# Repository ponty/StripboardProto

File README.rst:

StripboardProto

Stripboard_ based modular hardware prototyping system.

Links:
 * home: https://github.com/ponty/StripboardProto
 * documentation: http://ponty.github.com/StripboardProto

Features:
 - designed for hobby projects
 - stripboard_ based
 - no drilling
 - no etching
 - modular 
 - the bus consists of 8 bit ports
 - passive backplane_ holds the modules
 - Design tool: `EAGLE Light Edition`_
 
Example::

    backplane 
    
    II
    II
    II=C=================      microcontroller module    
    II
    II
    II=C=================      sound module
    II
    II
    II=C=================      USB module
    II

Bus:: 

    -----------------------------------------------               -----------
    | Port 1                                      |               | Port 2 
    -------------------------------------------------------------------------
    | 0 | 1 | 2 | 3 | 4 | 5 | 6 | 7 | POWER | GND | EMPTY | EMPTY | 0 | 1 ... 
    -------------------------------------------------------------------------

other modular designs:
 - http://www.instructables.com/id/AVR-mini-board-with-additional-boards/
 - Arduino shield

.. _`EAGLE Light Edition`: http://www.cadsoftusa.com/freeware.htm
.. _`Backplane`: http://en.wikipedia.org/wiki/Backplane
.. _Stripboard: http://en.wikipedia.org/wiki/Stripboard

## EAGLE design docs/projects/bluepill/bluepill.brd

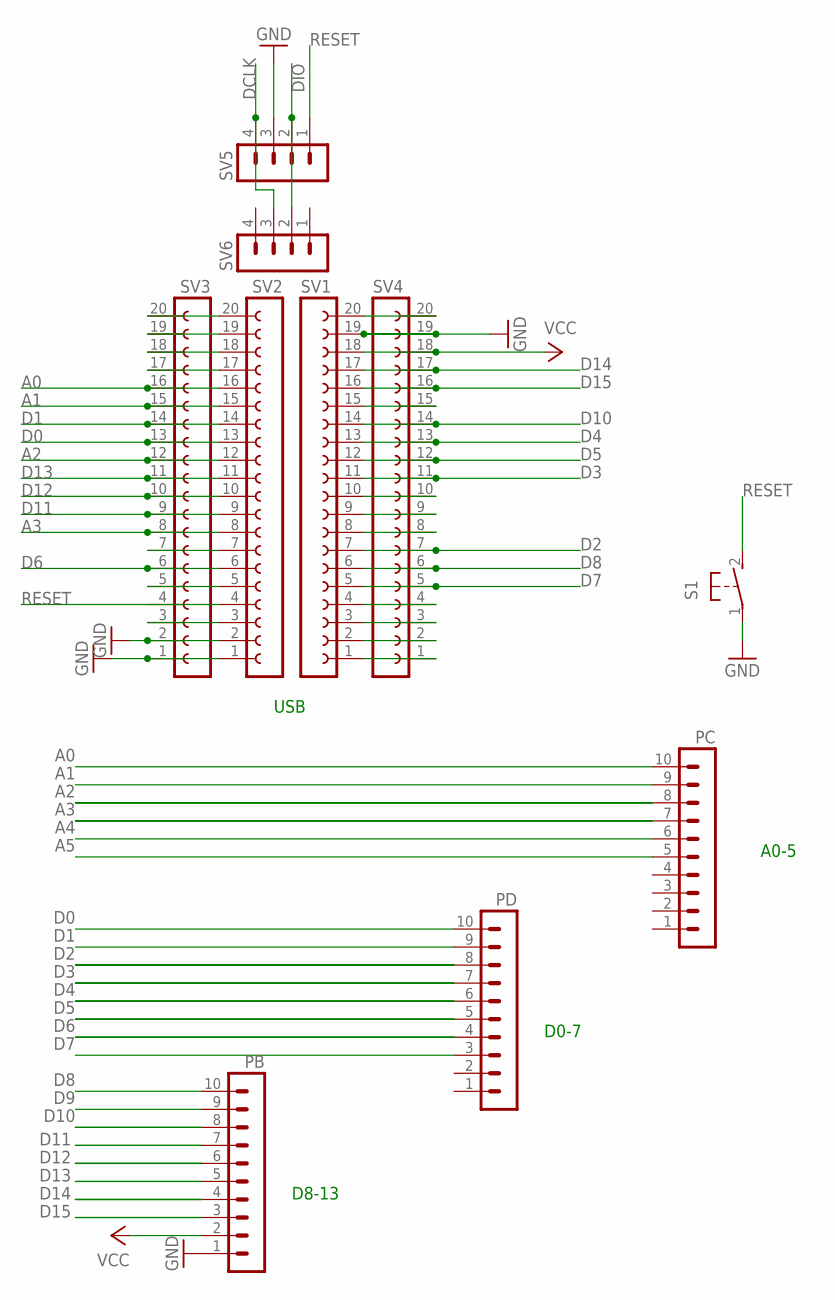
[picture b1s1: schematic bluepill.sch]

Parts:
PB: MA10-1W
PC: MA10-1W
PD: MA10-1W
S1: 31-XX; B3F-31XX
SV1, SV2, SV3, SV4: FE20-1; FE20
SV5, SV6: MA04-1

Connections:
A0: PC.10, SV2.16, SV3.16
A1: PC.9, SV2.15, SV3.15
A2: PC.8, SV2.12, SV3.12
A3: PC.7, SV2.8, SV3.8
A4: PC.6
A5: PC.5
D0: PD.10, SV2.13, SV3.13
D1: PD.9, SV2.14, SV3.14
D2: PD.8, SV1.7, SV4.7
D3: PD.7, SV1.11, SV4.11
D4: PD.6, SV1.13, SV4.13
D5: PD.5, SV1.12, SV4.12
D6: PD.4, SV2.6, SV3.6
D7: PD.3, SV1.5, SV4.5
D8: PB.10, SV1.6, SV4.6
D9: PB.9
D10: PB.8, SV1.14, SV4.14
D11: PB.7, SV2.9, SV3.9
D12: PB.6, SV2.10, SV3.10
D13: PB.5, SV2.11, SV3.11
D14: PB.4, SV1.17, SV4.17
D15: PB.3, SV1.16, SV4.16
DCLK: SV5.4, SV6.3
DIO: SV5.2, SV6.2
GND: PB.1, S1.1, SV1.19, SV2.1, SV2.2, SV3.1, SV3.2, SV4.19, SV5.3
unnamed: SV2.3, SV3.3
unnamed: SV2.5, SV3.5
unnamed: SV2.7, SV3.7
unnamed: SV2.17, SV3.17
unnamed: SV2.18, SV3.18
unnamed: SV2.19, SV3.19
unnamed: SV2.20, SV3.20
unnamed: SV1.1, SV4.1
unnamed: SV1.2, SV4.2
unnamed: SV1.3, SV4.3
unnamed: SV1.4, SV4.4
unnamed: SV1.8, SV4.8
unnamed: SV1.9, SV4.9
unnamed: SV1.10, SV4.10
unnamed: SV1.15, SV4.15
unnamed: SV1.20, SV4.20
RESET: S1.2 (S), SV2.4, SV3.4, SV5.1
VCC: PB.2, SV1.18, SV4.18

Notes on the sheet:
D0-7
D8-13
A0-5
USB

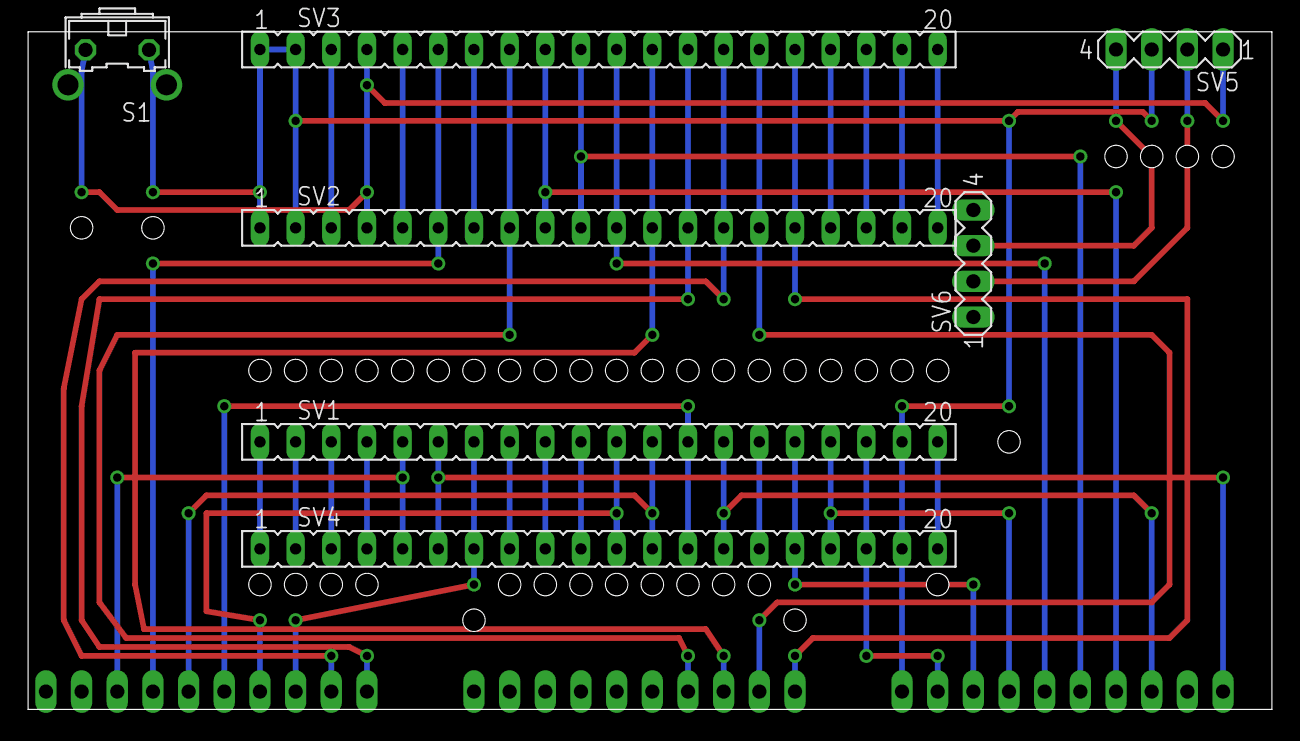
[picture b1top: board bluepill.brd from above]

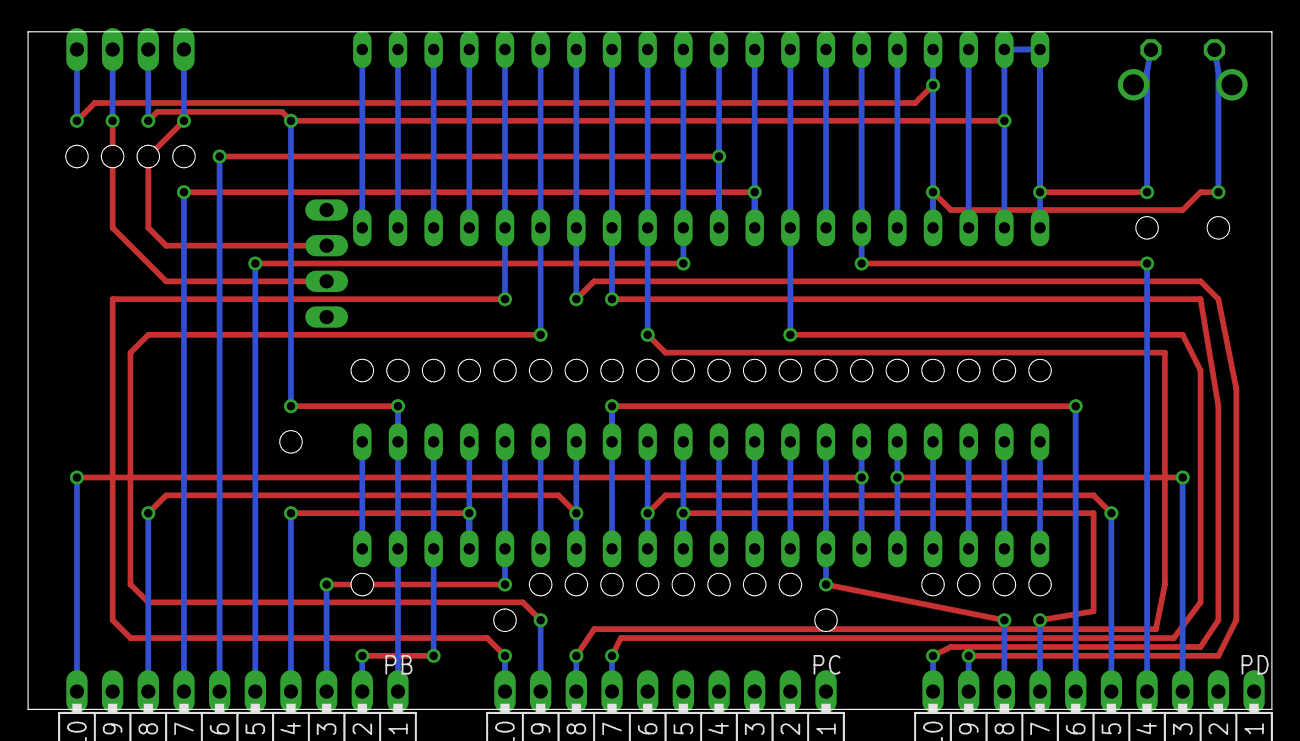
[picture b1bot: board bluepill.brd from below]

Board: 2 copper layers, 88.6 x 48.2 mm, 10 parts (3 on the bottom side), 40 nets.

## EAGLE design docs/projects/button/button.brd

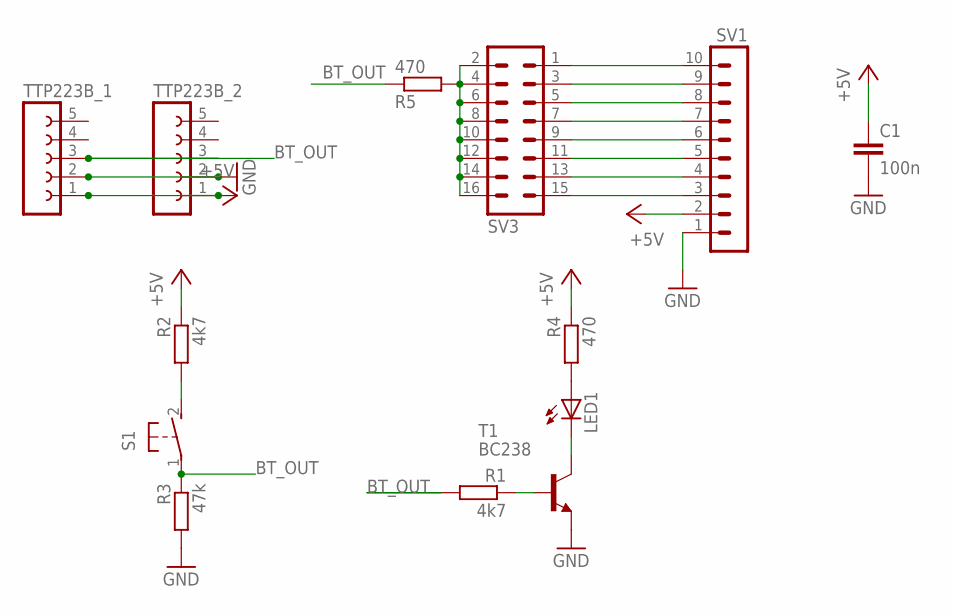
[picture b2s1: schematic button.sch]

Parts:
C1: 100n; C025-024X044
LED1: LED5MM
R1: 4k7; 0309/10
R2: 4k7; R0805
R3: 47k; 0414/15
R4, R5: 470; 0207/7
S1: 31-XX; B3F-31XX
SV1: MA10-1W
SV3: MA08-2
T1: BC238; TO5
TTP223B_1: FE05-1
TTP223B_2: FE05W

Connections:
+5V: C1.1, R2.1, R4.1, SV1.2, TTP223B_1.1, TTP223B_2.1
BT_OUT: R1.2, R3.1, R5.1, S1.1, TTP223B_1.3, TTP223B_2.3
GND: C1.2, R3.2, SV1.1, T1.1 (E), TTP223B_1.2, TTP223B_2.2
unnamed: R5.2, SV3.2, SV3.4, SV3.6, SV3.8, SV3.10, SV3.12, SV3.14, SV3.16
unnamed: LED1.K (C), T1.3 (C)
unnamed: R1.1, T1.2 (B)
unnamed: R2.2, S1.2 (S)
unnamed: LED1.A, R4.2
unnamed: SV1.3, SV3.15
unnamed: SV1.4, SV3.13
unnamed: SV1.5, SV3.11
unnamed: SV1.6, SV3.9
unnamed: SV1.7, SV3.7
unnamed: SV1.8, SV3.5
unnamed: SV1.9, SV3.3
unnamed: SV1.10, SV3.1

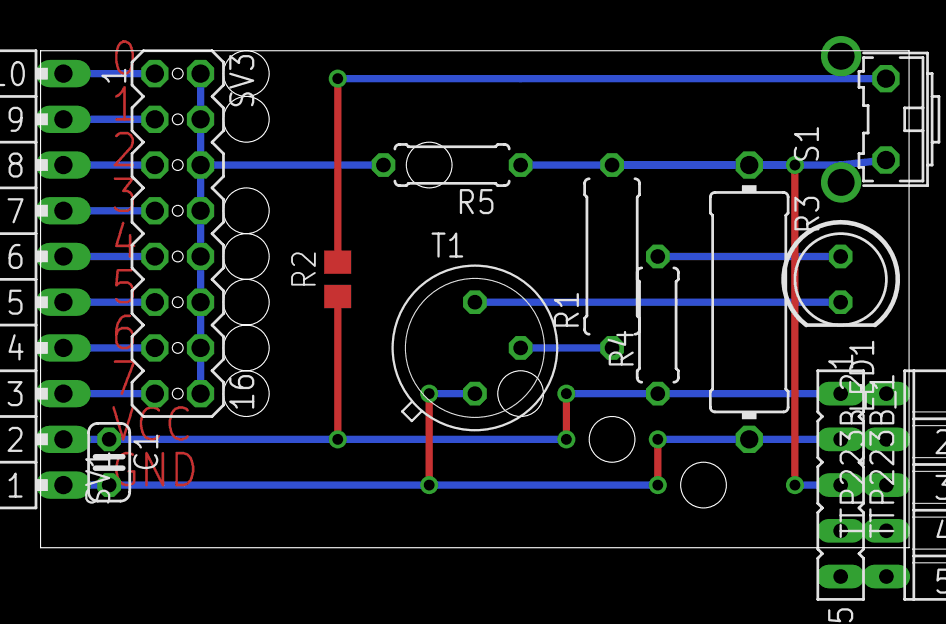
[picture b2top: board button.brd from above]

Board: 2 copper layers, 48.2 x 27.6 mm, 13 parts (0 on the bottom side), 16 nets.

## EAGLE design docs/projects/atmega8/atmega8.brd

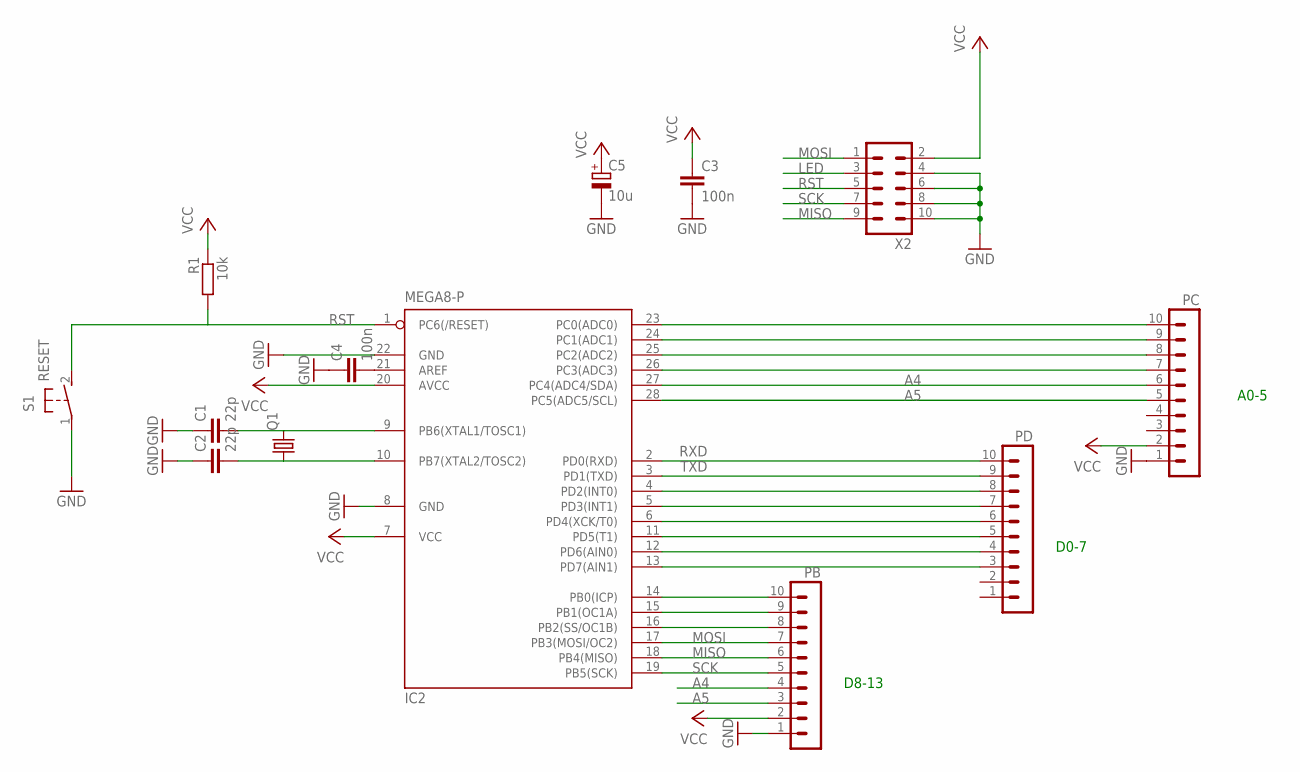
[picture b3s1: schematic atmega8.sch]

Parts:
C1: 22p; C025-024X044
C2: 22p; C050-025X075
C3, C4: 100n; C025-024X044
C5: 10u; E2,5-6E
IC2: MEGA8-P; DIL28-3
PB: MA10-1W
PC: MA10-1W
PD: MA10-1W
Q1: CRYSTALTC26V; TC26V
R1: 10k; 0204/7
S1: RESET; B3F-31XX
X2: ML10L

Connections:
A4: IC2.27 (PC4(ADC4/SDA)), PB.4, PC.6
A5: IC2.28 (PC5(ADC5/SCL)), PB.3, PC.5
GND: C1.1, C2.1, C3.2, C4.1, C5.-, IC2.8 (GND), IC2.22 (GND), PB.1, PC.1, S1.1, X2.4, X2.6, X2.8, X2.10
LED: X2.3
MISO: IC2.18 (PB4(MISO)), PB.6, X2.9
MOSI: IC2.17 (PB3(MOSI/OC2)), PB.7, X2.1
unnamed: IC2.11 (PD5(T1)), PD.5
unnamed: IC2.23 (PC0(ADC0)), PC.10
unnamed: IC2.13 (PD7(AIN1)), PD.3
unnamed: IC2.24 (PC1(ADC1)), PC.9
unnamed: IC2.25 (PC2(ADC2)), PC.8
unnamed: IC2.26 (PC3(ADC3)), PC.7
unnamed: IC2.4 (PD2(INT0)), PD.8
unnamed: IC2.5 (PD3(INT1)), PD.7
unnamed: IC2.6 (PD4(XCK/T0)), PD.6
unnamed: C4.2, IC2.21 (AREF)
unnamed: IC2.12 (PD6(AIN0)), PD.4
unnamed: IC2.1 (PC6(/RESET)), R1.2, S1.2 (S)
unnamed: IC2.15 (PB1(OC1A)), PB.9
unnamed: C1.2, IC2.9 (PB6(XTAL1/TOSC1)), Q1.2
unnamed: C2.2, IC2.10 (PB7(XTAL2/TOSC2)), Q1.1
unnamed: IC2.14 (PB0(ICP)), PB.10
unnamed: IC2.16 (PB2(SS/OC1B)), PB.8
RST: X2.5
RXD: IC2.2 (PD0(RXD)), PD.10
SCK: IC2.19 (PB5(SCK)), PB.5, X2.7
TXD: IC2.3 (PD1(TXD)), PD.9
VCC: C3.1, C5.+, IC2.7 (VCC), IC2.20 (AVCC), PB.2, PC.2, R1.1, X2.2

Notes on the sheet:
D0-7
D8-13
A0-5

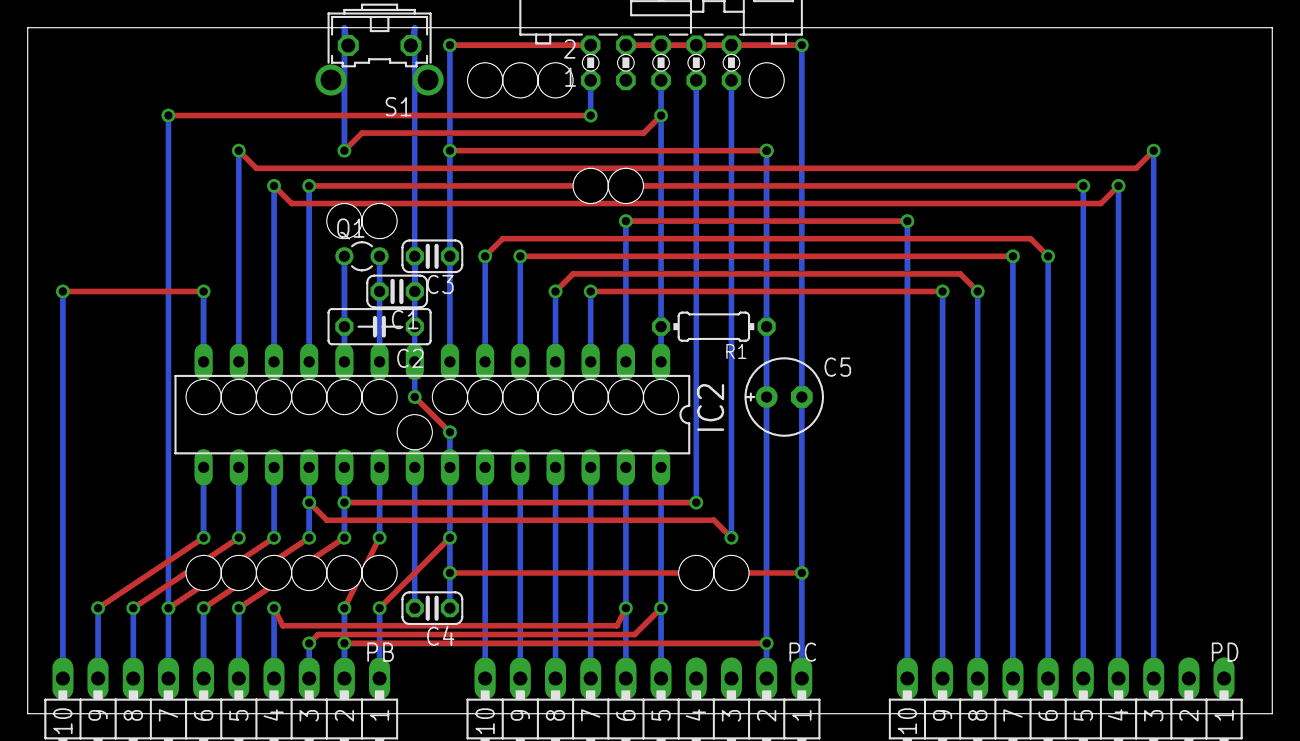
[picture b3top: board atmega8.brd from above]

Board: 2 copper layers, 89.8 x 49.5 mm, 13 parts (0 on the bottom side), 26 nets.

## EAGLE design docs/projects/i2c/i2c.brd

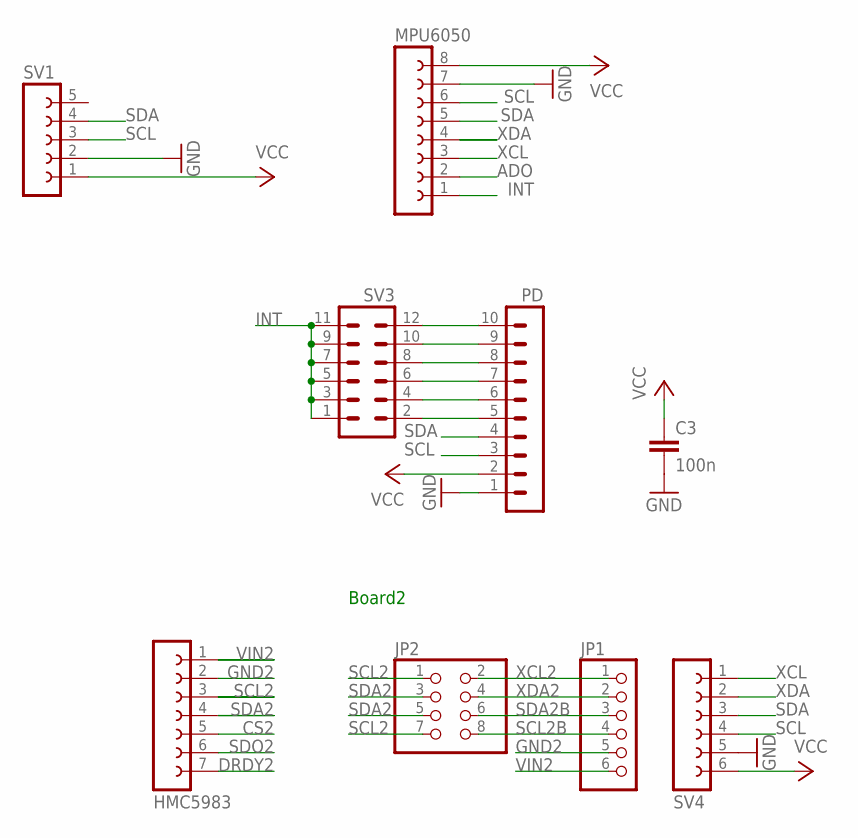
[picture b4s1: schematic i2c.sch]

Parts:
C3: 100n; C025-024X044
HMC5983: FE07-1; FE07
JP1: PINHD-1X6/90; 1X06/90
JP2: PINHD-2X4; 2X04
MPU6050: FE08W
PD: MA10-1W
SV1: FE05-1
SV3: MA06-2
SV4: FE06-1; FE06

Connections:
ADO: MPU6050.2
CS2: HMC5983.5
DRDY2: HMC5983.7
GND: C3.2, MPU6050.7, PD.1, SV1.2, SV4.5
GND2: HMC5983.2, JP1.5
INT: MPU6050.1, SV3.1, SV3.3, SV3.5, SV3.7, SV3.9, SV3.11
unnamed: PD.10, SV3.12
unnamed: PD.9, SV3.10
unnamed: PD.8, SV3.8
unnamed: PD.7, SV3.6
unnamed: PD.6, SV3.4
unnamed: PD.5, SV3.2
SCL: MPU6050.6, PD.3, SV1.3, SV4.4
SCL2: HMC5983.3, JP2.1, JP2.7
SCL2B: JP1.4, JP2.8
SDA: MPU6050.5, PD.4, SV1.4, SV4.3
SDA2: HMC5983.4, JP2.3, JP2.5
SDA2B: JP1.3, JP2.6
SDO2: HMC5983.6
VCC: C3.1, MPU6050.8, PD.2, SV1.1, SV4.6
VIN2: HMC5983.1, JP1.6
XCL: MPU6050.3, SV4.1
XCL2: JP1.1, JP2.2
XDA: MPU6050.4, SV4.2
XDA2: JP1.2, JP2.4

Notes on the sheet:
Board2

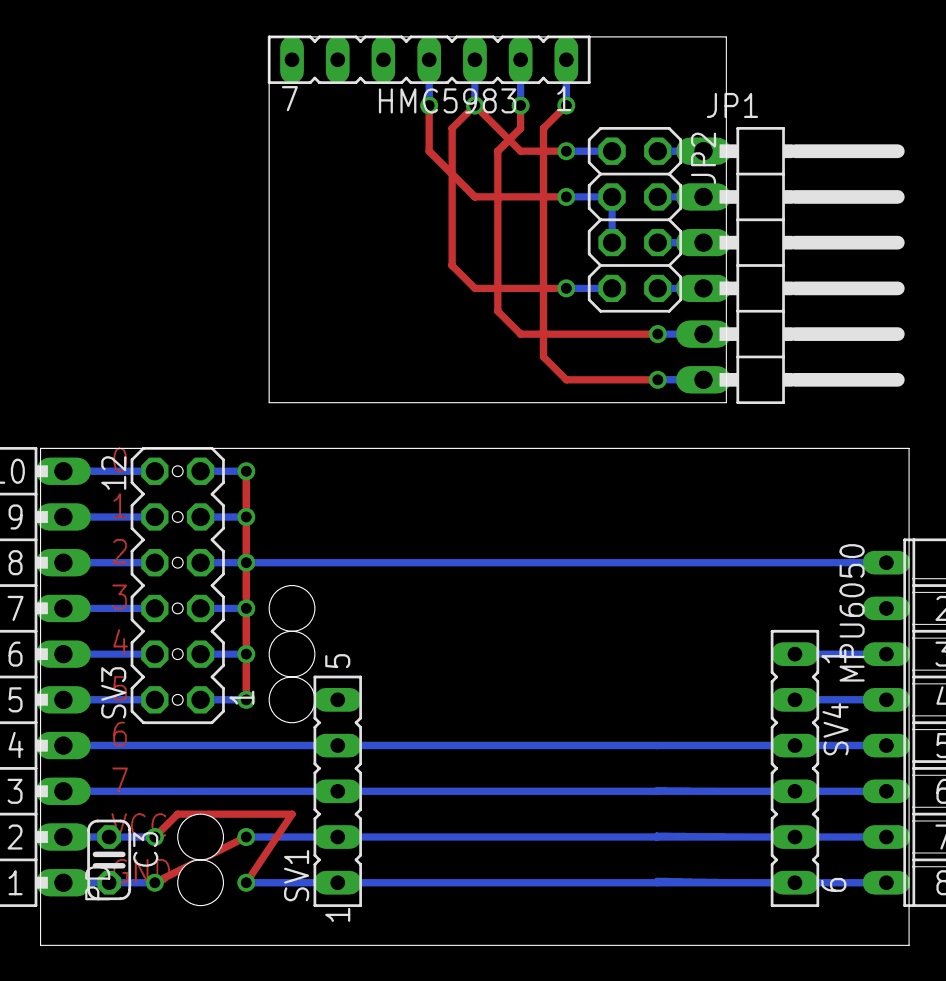
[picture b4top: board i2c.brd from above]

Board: 2 copper layers, 48.2 x 50.5 mm, 9 parts (0 on the bottom side), 21 nets.

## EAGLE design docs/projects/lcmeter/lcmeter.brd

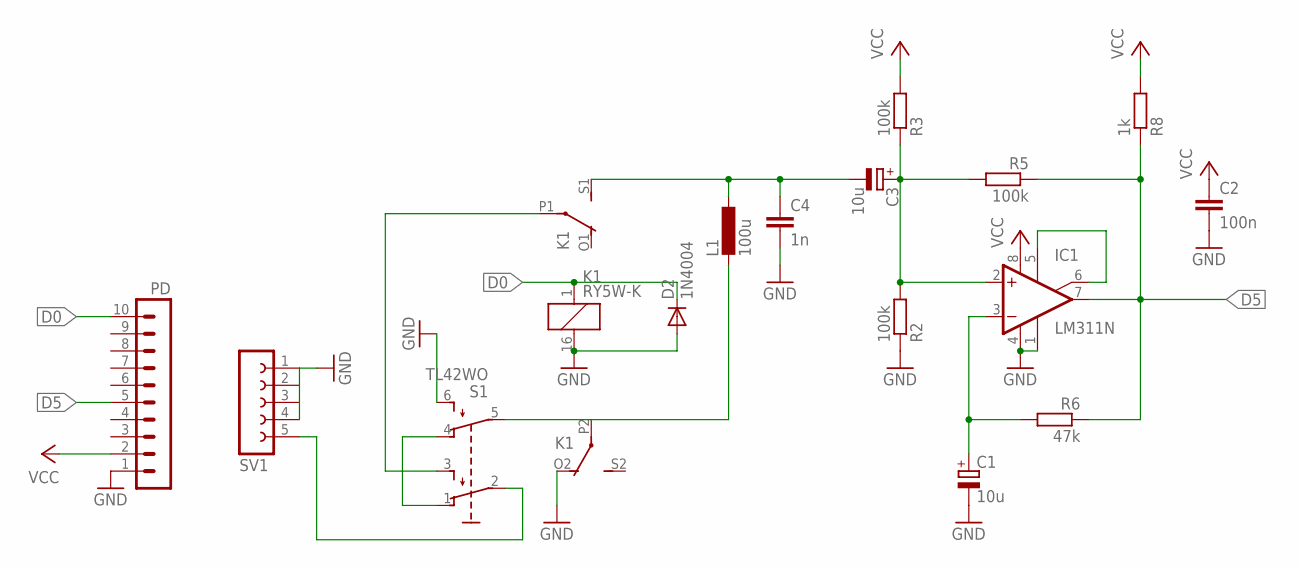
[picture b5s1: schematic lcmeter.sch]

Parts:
C1: 10u; E2,5-6
C2: 100n; C025-024X044
C3: 10u; TT5D7
C4: 1n; C050-025X075
D2: 1N4004; DO35-7
IC1: LM311N; DIL08
K1: RY5W-K; 351
L1: 100u; 0204/7
PD: MA10-1W
R2: 100k; 0207/10
R3, R5: 100k; 0204/7
R6: 47k; 0204/5
R8: 1k; 0204/7
S1: TL42WO; TL4XWO
SV1: FE05W

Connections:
D0: D2.C, K1.1, PD.10
D5: IC1.7 (OUT), PD.5, R5.1, R6.1, R8.1
GND: C1.-, C2.2, C4.2, D2.A, IC1.1 (GND), IC1.4 (V-), K1.16 (2), K1.O2 (O), PD.1, R2.1, S1.6 (S1), SV1.1, SV1.2, SV1.3, SV1.4
unnamed: IC1.5 (ON), IC1.6 (ON/STR)
unnamed: C3.+, IC1.2 (+IN), R2.2, R3.1, R5.2
unnamed: C1.+, IC1.3 (-IN), R6.2
unnamed: S1.1 (O), S1.4 (O1)
unnamed: K1.P2, L1.2, S1.5 (P1)
unnamed: C3.-, C4.1, K1.S1 (S), L1.1
unnamed: S1.2, SV1.5
unnamed: K1.P1, S1.3 (S)
VCC: C2.1, IC1.8 (V+), PD.2, R3.2, R8.2

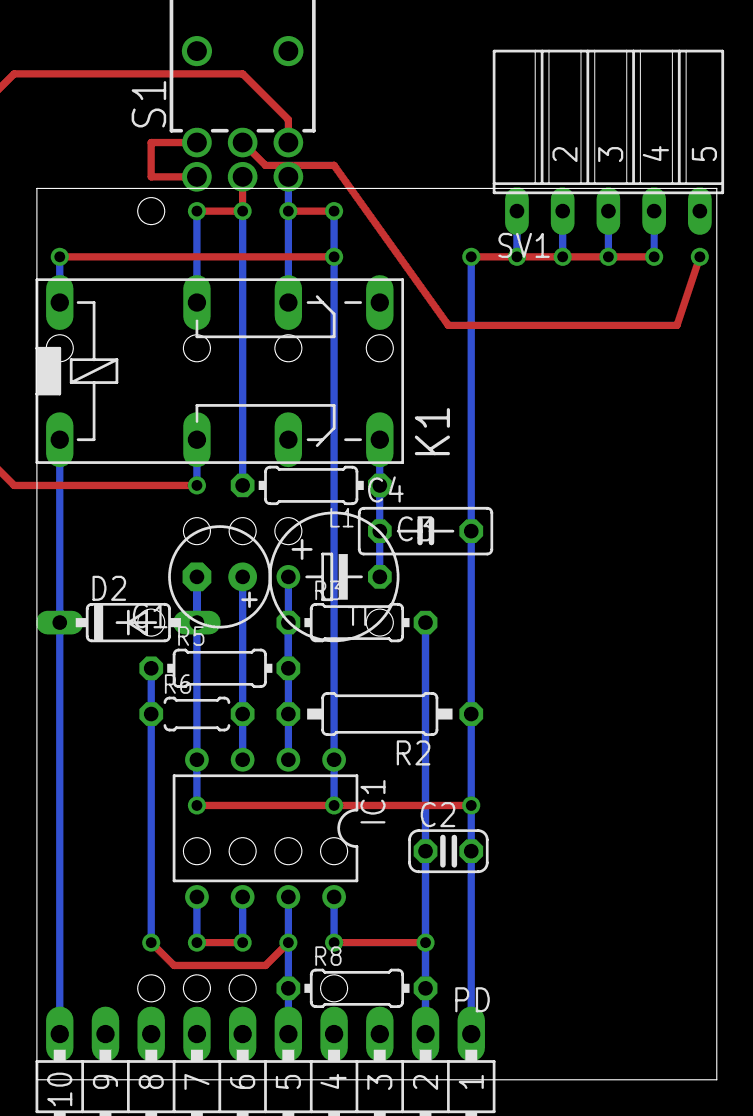
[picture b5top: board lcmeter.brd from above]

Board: 2 copper layers, 37.8 x 49.5 mm, 16 parts (0 on the bottom side), 12 nets.

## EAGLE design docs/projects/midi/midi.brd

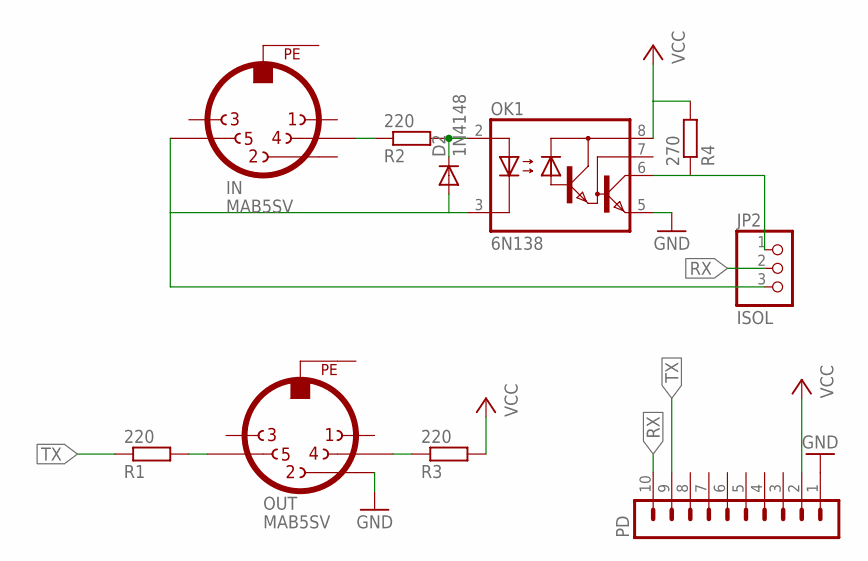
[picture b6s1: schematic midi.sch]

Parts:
D2: 1N4148; D-2.5
IN: MAB5SV
JP2: ISOL; 1X03/90
OK1: 6N138; DIL08
OUT: MAB5SV
PD: MA10-1W
R1, R2: 220; 0204/7
R3: 220; 0207/12
R4: 270; 0204/5

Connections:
GND: OK1.5 (GND), OUT.2, PD.1
unnamed: OUT.4, R3.1
unnamed: OUT.5, R1.2
unnamed: D2.A, IN.5, JP2.3, OK1.3 (C)
unnamed: D2.C, OK1.2 (A), R2.2
unnamed: IN.4, R2.1
unnamed: JP2.1, OK1.6 (VO), R4.1
PE: IN.PE, OUT.PE
RX: JP2.2, PD.10
TX: PD.9, R1.1
VCC: OK1.8 (VCC), PD.2, R3.2, R4.2

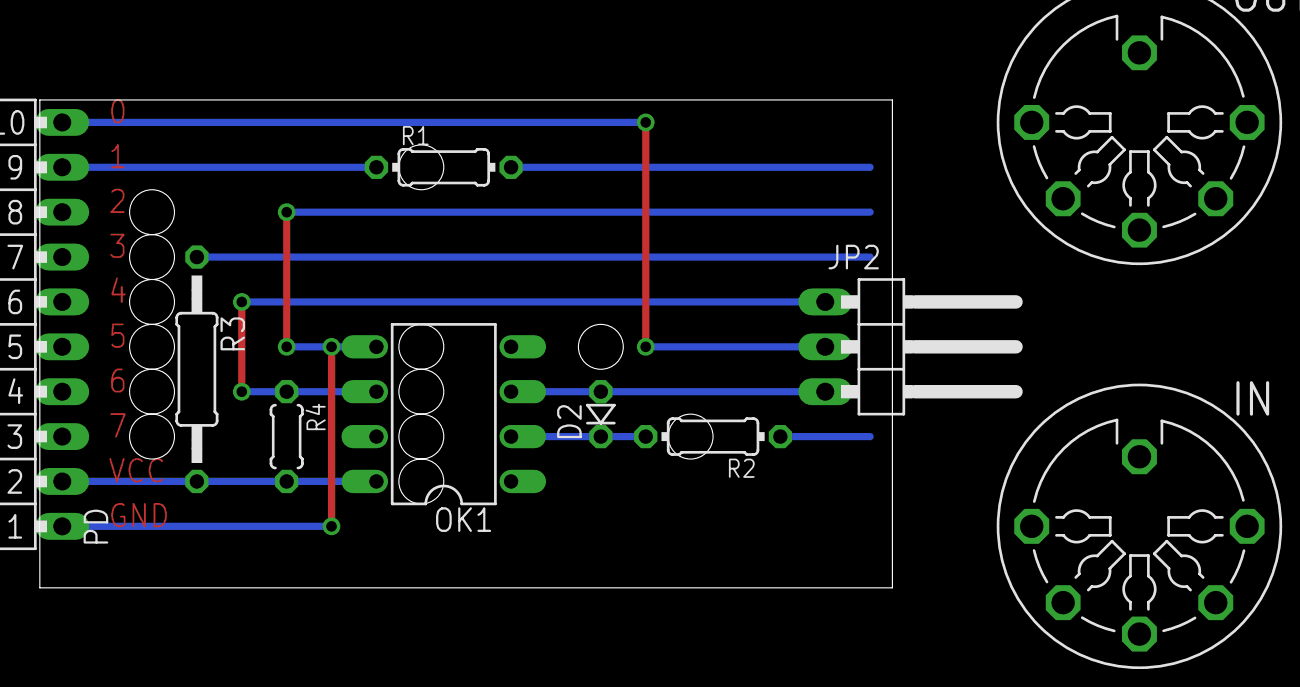
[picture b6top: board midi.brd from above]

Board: 2 copper layers, 48.2 x 27.6 mm, 10 parts (0 on the bottom side), 11 nets.

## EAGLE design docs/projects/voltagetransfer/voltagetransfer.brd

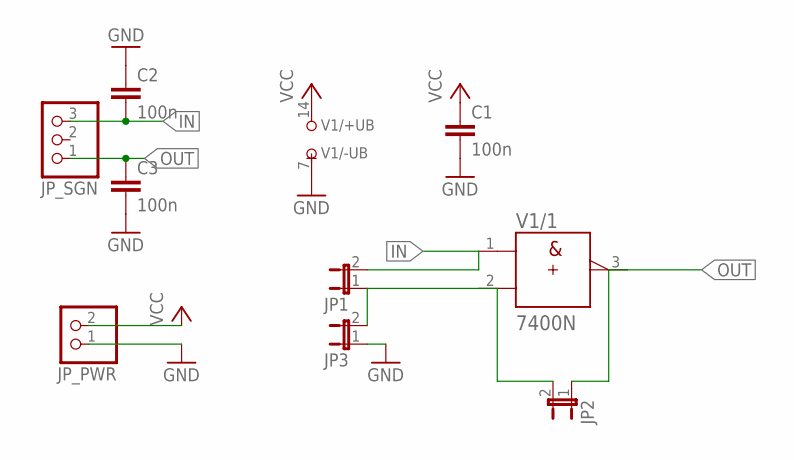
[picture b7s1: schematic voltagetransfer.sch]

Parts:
C1, C2, C3: 100n; C025-024X044
JP1, JP2, JP3: JP1E; JP1
JP_PWR: PINHD-1X2/90; 1X02/90
JP_SGN: PINHD-1X3/90; 1X03/90
V1: 7400N; DIL14

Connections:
GND: C1.2, C2.1, C3.2, JP3.1, JP_PWR.1, V1.7 (-UB)
IN: C2.2, JP1.2, JP_SGN.3, V1.1 (A)
unnamed: JP1.1, JP2.2, JP3.2, V1.2 (B)
OUT: C3.1, JP2.1, JP_SGN.1, V1.3 (Y)
VCC: C1.1, JP_PWR.2, V1.14 (+UB)

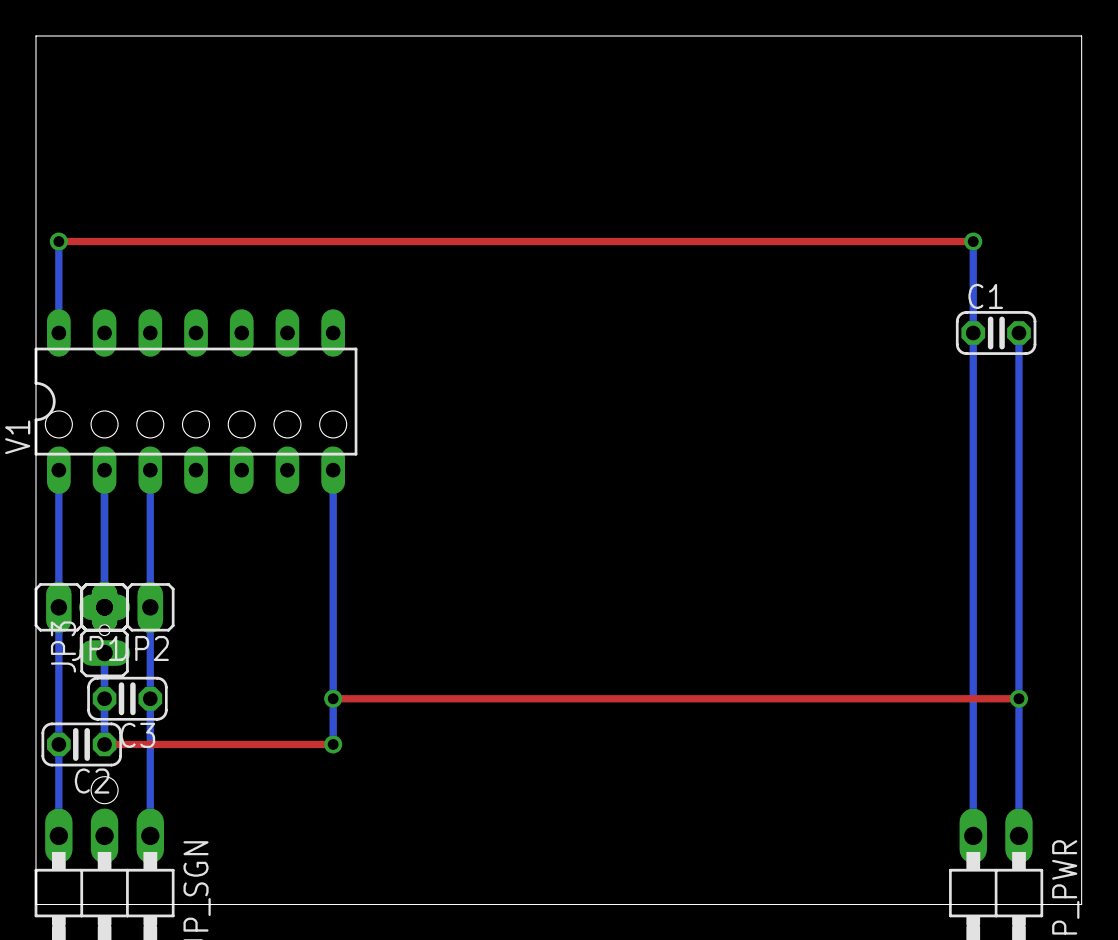
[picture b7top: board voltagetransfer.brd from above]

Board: 2 copper layers, 58.1 x 48.2 mm, 9 parts (0 on the bottom side), 5 nets.

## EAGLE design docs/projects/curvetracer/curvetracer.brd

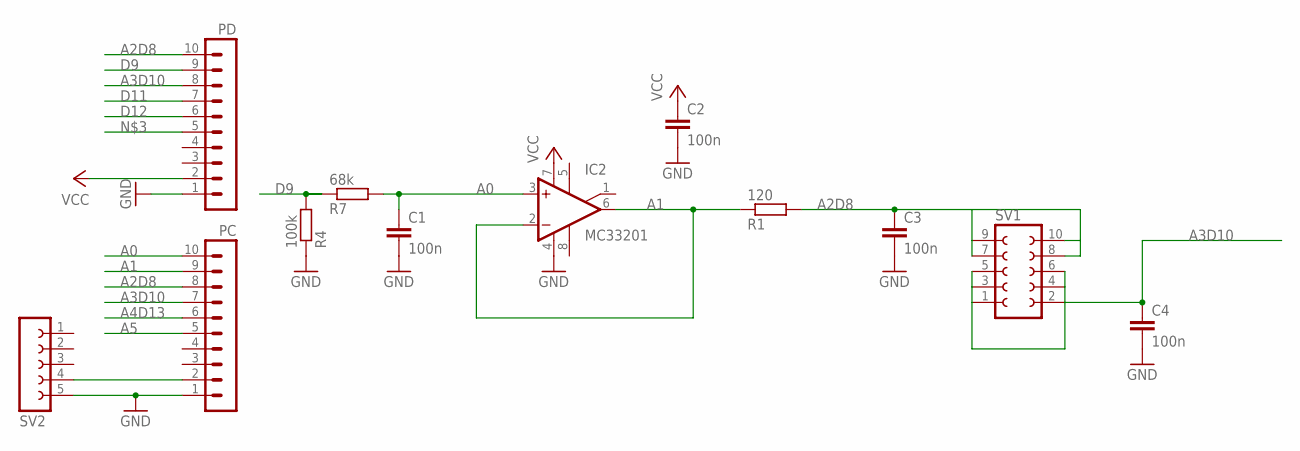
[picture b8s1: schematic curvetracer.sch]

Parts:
C1, C2: 100n; C025-024X044
C3: 100n; C075-032X103
C4: 100n; C102-043X133
IC2: MC33201; DIL08
PC: MA10-1W
PD: MA10-1W
R1: 120; R1206
R4: 100k; R1206
R7: 68k; R1206
SV1: FE05-2W
SV2: FE05W

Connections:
A0: C1.1, IC2.3 (+IN), PC.10, R7.2
A1: IC2.2 (-IN), IC2.6 (OUT), PC.9, R1.1
A2D8: C3.1, PC.8, PD.10, R1.2, SV1.7, SV1.8, SV1.9, SV1.10
A3D10: C4.1, PC.7, PD.8, SV1.1, SV1.2, SV1.3, SV1.4, SV1.5, SV1.6
A4D13: PC.6
A5: PC.5
D9: PD.9, R4.2, R7.1
D11: PD.7
D12: PD.6
GND: C1.2, C2.2, C3.2, C4.2, IC2.4 (V-), PC.1, PD.1, R4.1, SV2.5
unnamed: PC.2, SV2.4
VCC: C2.1, IC2.7 (V+), PD.2

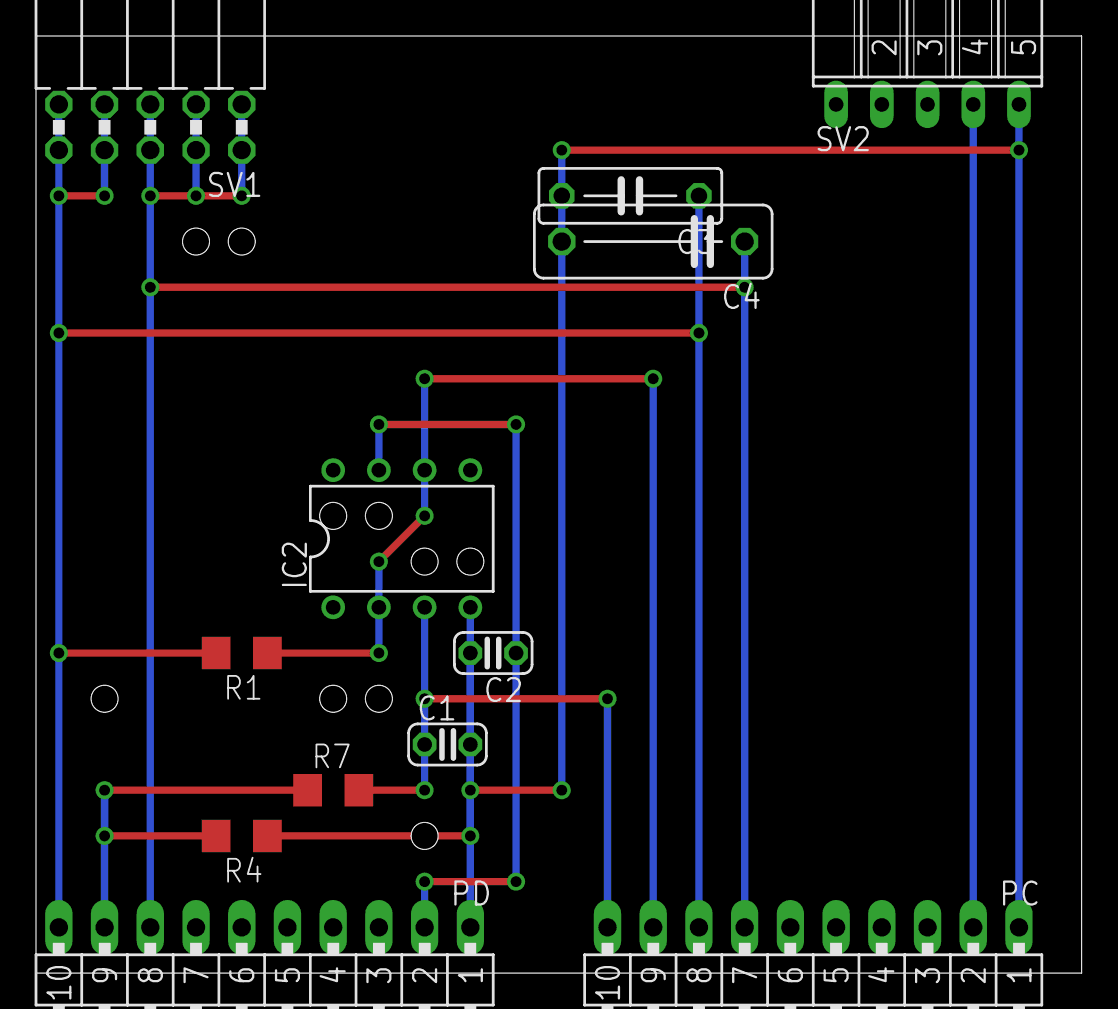
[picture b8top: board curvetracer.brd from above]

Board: 2 copper layers, 58.1 x 52.1 mm, 12 parts (0 on the bottom side), 8 nets.

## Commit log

2011-12-28 start
2011-12-28 Update documentation
2011-12-29 fix doc
2011-12-29 more doc
2011-12-29 new board: backplane
2012-03-12 new:tvout
2012-03-12 tasks
2012-03-12 new: ladder dac
2012-03-15 fix wire
2012-04-21 new: esr meter
2012-04-21 new: curve tracer
2012-04-21 page break
2012-04-21 new: opamp swing
2012-04-21 change text color
2012-11-01 upgrade eagle files to XML
2012-12-02 better clean filter
2012-12-03 formatting by autopep8
2012-12-03 new project: busmonitor
2013-01-30 esrmeter: modify schematic
2013-02-13 fix airwires
2013-03-17 simplified pavement tasks
2013-08-11 support for voltagetransfer
2013-08-11 new project: voltagetransfer
2013-08-11 generated doc
2014-04-09 new midi interface
2014-04-09 new lcmeter
2017-01-16 midi
2017-01-20 test tools
2017-01-20 fix underlines
2017-01-23 pavement
2017-01-23 vagrant: add latex
2017-01-23 conf.py
2017-01-23 bluepill
2017-01-23 remove blank pages from pdf
2017-01-23 busmonitor: add missing png files
2017-01-23 gitignore
2017-02-28 atmega8: 6,7 is connected with 14,15 to make I2C compatible with Nucleo
2017-02-28 git ignore pdf
2017-02-28 button
2017-02-28 bluepill: fix order
